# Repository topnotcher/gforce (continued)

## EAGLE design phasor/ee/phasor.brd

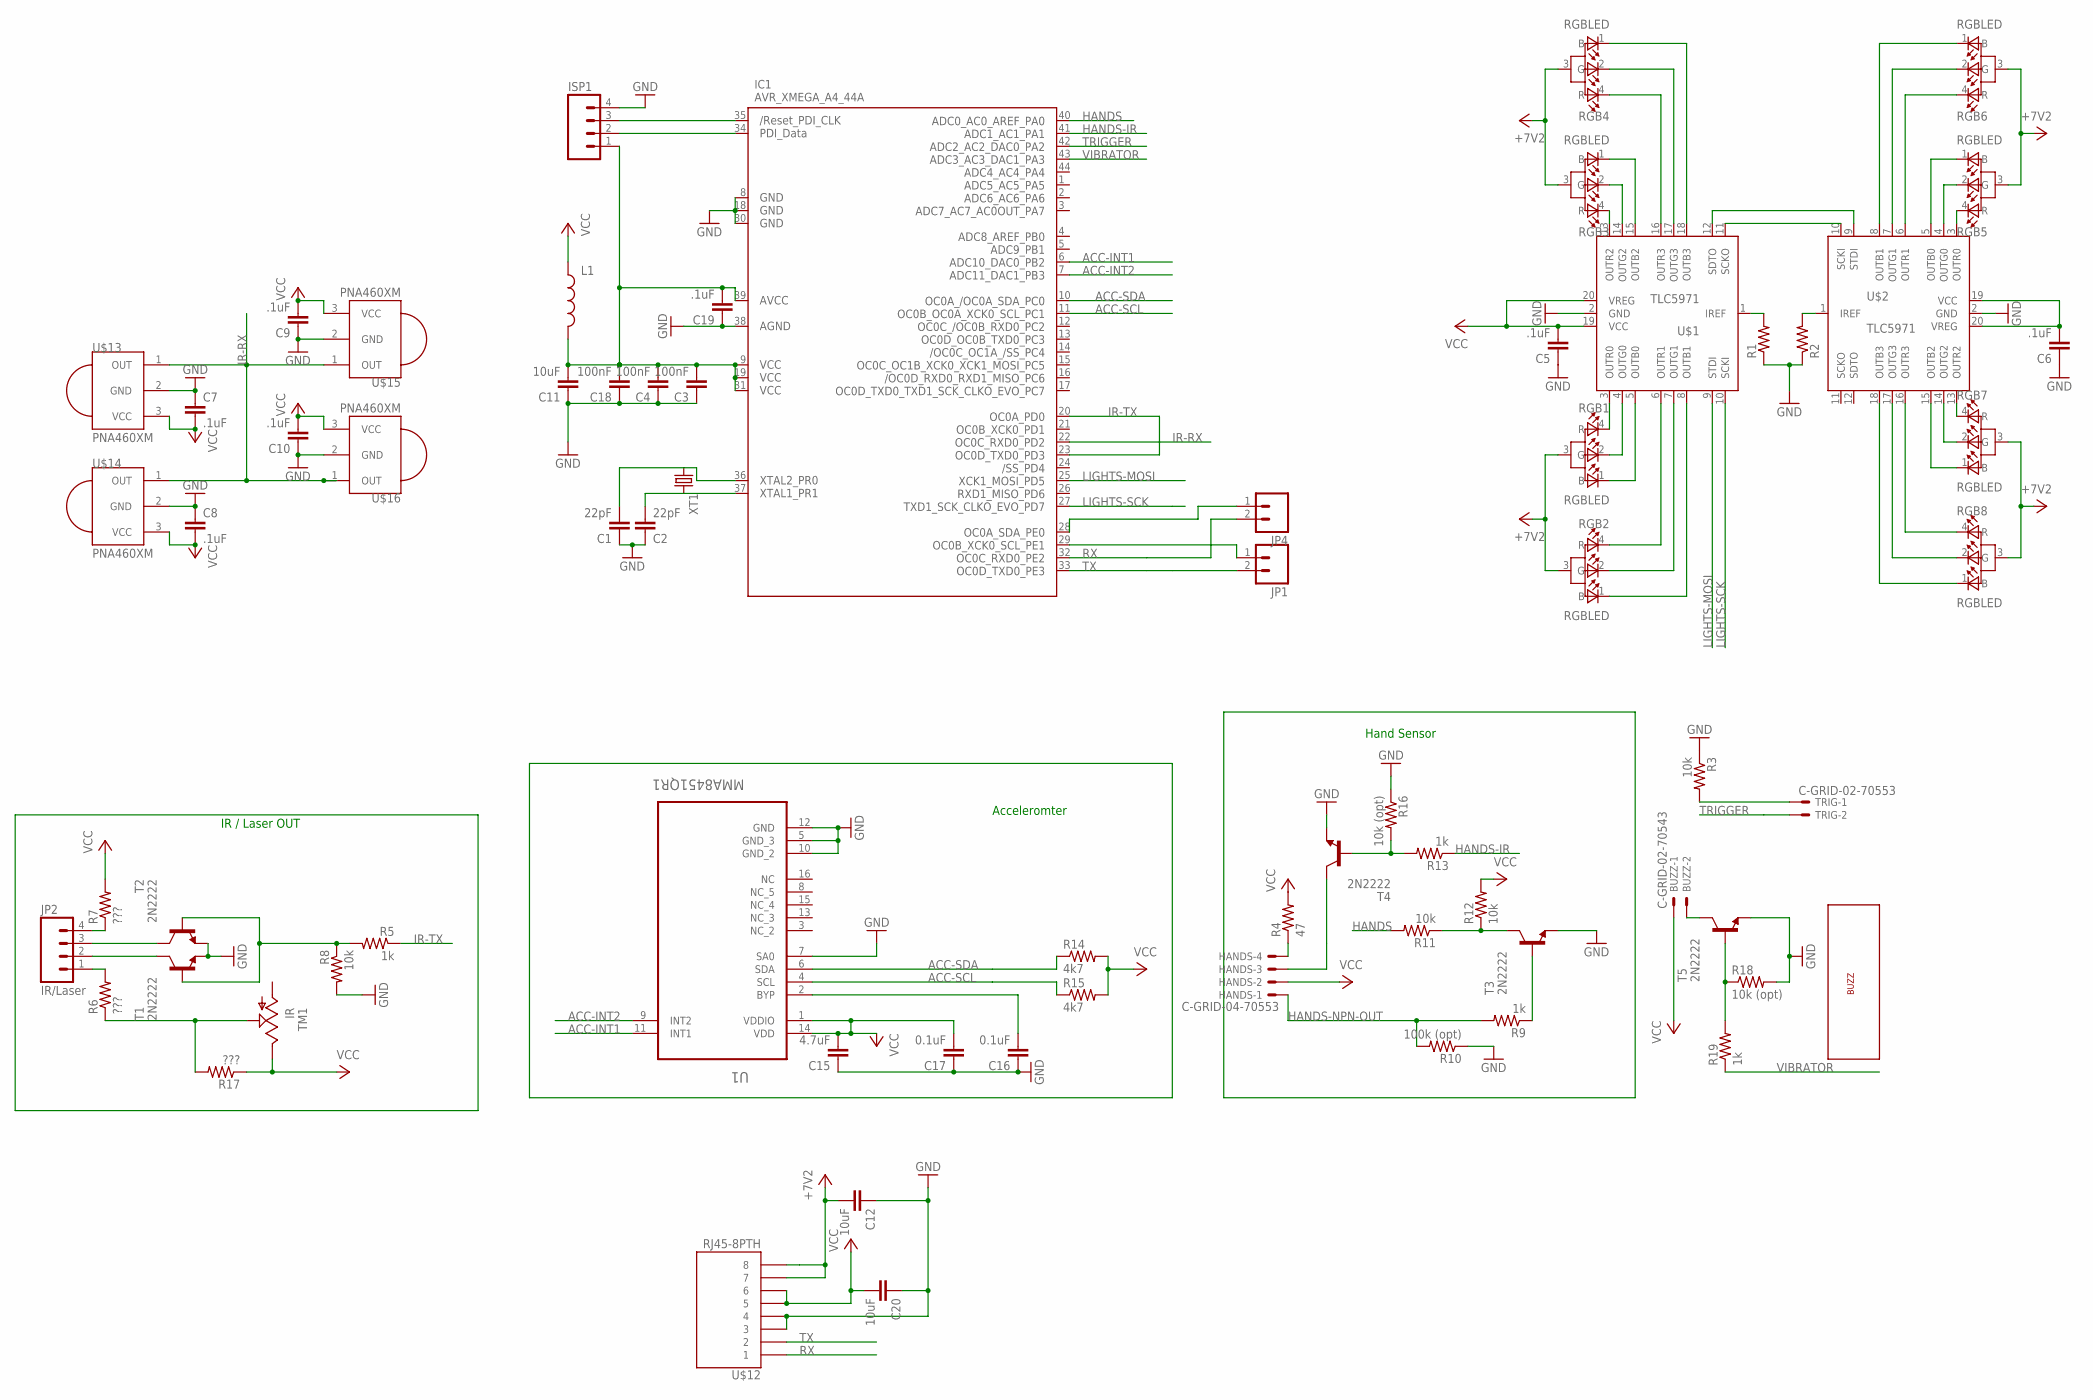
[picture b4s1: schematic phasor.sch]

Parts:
BUZZ: C-GRID-02-70543; 70543-02
C1, C2: 22pF; CAP-PTH-SMALL
C3, C4, C18: 100nF; 0603-CAP
C5, C6, C7, C8, C9, C10: .1uF; CAP-PTH-SMALL
C11, C12, C20: 10uF; 1206
C15: 4.7uF; 0805
C16, C17: 0.1uF; 0603-CAP
C19: .1uF; 0603-CAP
HANDS: C-GRID-04-70553; 70553-04
IC1: AVR_XMEGA_A4_44A; TQFP44
ISP1: M04LOCK; 1X04_LOCK
JP1, JP4: M02PTH; 1X02
JP2: IR/Laser; 1X04_LOCK
L1: INDUCTOR1206H*; 1206
R1, R2: R-US_0204/7; 0204/7
R3, R8, R11, R12: 10k; 0204/7
R4: 47; 0204/7
R5, R9, R13, R19: 1k; 0204/7
R6, R7, R17: ???; 0204/7
R10: 100k (opt); 0204/7
R14, R15: 4k7; 0204/7
R16, R18: 10k (opt); 0204/7
RGB1, RGB2, RGB3, RGB4, RGB5, RGB6, RGB7, RGB8: RGBLED; RGB-LED-10MM-COMMON-ANODE
T1, T2, T3, T4, T5: 2N2222; TO92-EBC-OVAL
TM1: IR; B25P
TRIG: C-GRID-02-70553; 70553-02
U1: MMA8451QR1; QFN50P300X300X100-16N
U$1, U$2: TLC5971; SSOP20
U$3: VIB-CAPSULE
U$12: RJ45-8PTH; RJ45-8
U$13, U$14, U$15, U$16: PNA460XM
XT1: CRYSTALHC49US; HC49US

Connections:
+7V2: C12.2, RGB1.3 (VCC), RGB2.3 (VCC), RGB3.3 (VCC), RGB4.3 (VCC), RGB5.3 (VCC), RGB6.3 (VCC), RGB7.3 (VCC), RGB8.3 (VCC), U$12.7, U$12.8
ACC-INT1: IC1.6 (PB2), U1.11 (INT1)
ACC-INT2: IC1.7 (PB3), U1.9 (INT2)
ACC-SCL: IC1.11 (PC1), R15.1, U1.4 (SCL)
ACC-SDA: IC1.10 (PC0), R14.1, U1.6 (SDA)
GND: C1.1, C2.1, C3.1, C4.1, C5.1, C6.1, C7.1, C8.1, C9.1, C10.1, C11.1, C12.1, C15.1, C16.1, C17.1, C18.1, C19.1, C20.1, IC1.8 (GND1), IC1.18 (GND2), IC1.30 (GND3), IC1.38 (AGND), ISP1.4, R1.1, R2.1, R3.1, R8.2, R10.1, R16.1, R18.2, T1.E, T2.E, T3.E, T4.E, T5.E, U1.5 (GND_3), U1.7 (SA0), U1.10 (GND_2), U1.12 (GND), U$1.2 (GND), U$2.2 (GND), U$12.3, U$12.4, U$13.2 (GND), U$14.2 (GND), U$15.2 (GND), U$16.2 (GND)
HANDS: IC1.40 (PA0), R11.2
HANDS-IR: IC1.41 (PA1), R13.1
HANDS-NPN-OUT: HANDS.1, R9.2, R10.2
IR-RX: IC1.22 (PD2), U$13.1 (OUT), U$14.1 (OUT), U$15.1 (OUT), U$16.1 (OUT)
IR-TX: IC1.20 (PD0), IC1.23 (PD3), R5.1
LIGHTS-MOSI: IC1.25 (PD5), U$1.9 (STDI)
LIGHTS-SCK: IC1.27 (PD7), U$1.10 (SCKI)
unnamed: U$1.11 (SCKO), U$2.10 (SCKI)
unnamed: U$1.12 (SDTO), U$2.9 (STDI)
unnamed: R1.2, U$1.1 (IREF)
unnamed: RGB1.4 (R), U$1.3 (OUTR0)
unnamed: RGB1.2 (G), U$1.4 (OUTG0)
unnamed: RGB1.1 (B), U$1.5 (OUTB0)
unnamed: RGB2.4 (R), U$1.6 (OUTR1)
unnamed: RGB2.2 (G), U$1.7 (OUTG1)
unnamed: RGB2.1 (B), U$1.8 (OUTB1)
unnamed: RGB3.1 (B), U$1.15 (OUTB2)
unnamed: RGB3.4 (R), U$1.13 (OUTR2)
unnamed: IC1.29 (PE1), JP1.1
unnamed: RGB4.4 (R), U$1.16 (OUTR3)
unnamed: BUZZ.2, T5.C
unnamed: RGB4.1 (B), U$1.18 (OUTB3)
unnamed: RGB5.4 (R), U$2.3 (OUTR0)
unnamed: RGB5.2 (G), U$2.4 (OUTG0)
unnamed: RGB5.1 (B), U$2.5 (OUTB0)
unnamed: R18.1, R19.2, T5.B
unnamed: RGB6.2 (G), U$2.7 (OUTG1)
unnamed: RGB6.1 (B), U$2.8 (OUTB1)
unnamed: RGB8.4 (R), U$2.16 (OUTR3)
unnamed: RGB8.2 (G), U$2.17 (OUTG3)
unnamed: RGB8.1 (B), U$2.18 (OUTB3)
unnamed: RGB7.1 (B), U$2.15 (OUTB2)
unnamed: RGB7.2 (G), U$2.14 (OUTG2)
unnamed: RGB7.4 (R), U$2.13 (OUTR2)
unnamed: C2.2, IC1.37 (PR1), XT1.2
unnamed: C1.2, IC1.36 (PR0), XT1.1
unnamed: R3.2, TRIG.1
unnamed: R6.1, R17.2, TM1.S
unnamed: HANDS.4, R4.1
unnamed: R9.1, T3.B
unnamed: R11.1, R12.1, T3.C
unnamed: R2.2, U$2.1 (IREF)
unnamed: C16.2, U1.2 (BYP)
unnamed: HANDS.3, T4.C
unnamed: JP2.1, R6.2
unnamed: JP2.2, T1.C
unnamed: JP2.4, R7.1
unnamed: JP2.3, T2.C
unnamed: R5.2, R8.1, T1.B, T2.B
unnamed: IC1.28 (PE0), JP4.1
unnamed: IC1.34 (PDI_DATA), ISP1.2
unnamed: R13.2, R16.2, T4.B
unnamed: IC1.35 (RESET), ISP1.3
unnamed: C3.2, C4.2, C11.2, C18.2, C19.2, IC1.9 (VCC1), IC1.19 (VCC2), IC1.31 (VCC3), IC1.39 (AVCC), ISP1.1, L1.2
RGB3: RGB3.2 (G), U$1.14 (OUTG2)
RGB4: RGB4.2 (G), U$1.17 (OUTG3)
RGB6: RGB6.4 (R), U$2.6 (OUTR1)
RX: IC1.32 (PE2), JP4.2, U$12.1
TRIGGER: IC1.42 (PA2), TRIG.2
TX: IC1.33 (PE3), JP1.2, U$12.2
VCC: BUZZ.1, C5.2, C6.2, C7.2, C8.2, C9.2, C10.2, C15.2, C17.2, C20.2, HANDS.2, L1.1, R4.2, R7.2, R12.2, R14.2, R15.2, R17.1, TM1.E, U1.1 (VDDIO), U1.14 (VDD), U$1.19 (VCC), U$1.20 (VREG), U$2.19 (VCC), U$2.20 (VREG), U$12.5, U$12.6, U$13.3 (VCC), U$14.3 (VCC), U$15.3 (VCC), U$16.3 (VCC)
VIBRATOR: IC1.43 (PA3), R19.1

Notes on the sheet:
IR / Laser OUT
Hand Sensor
Acceleromter

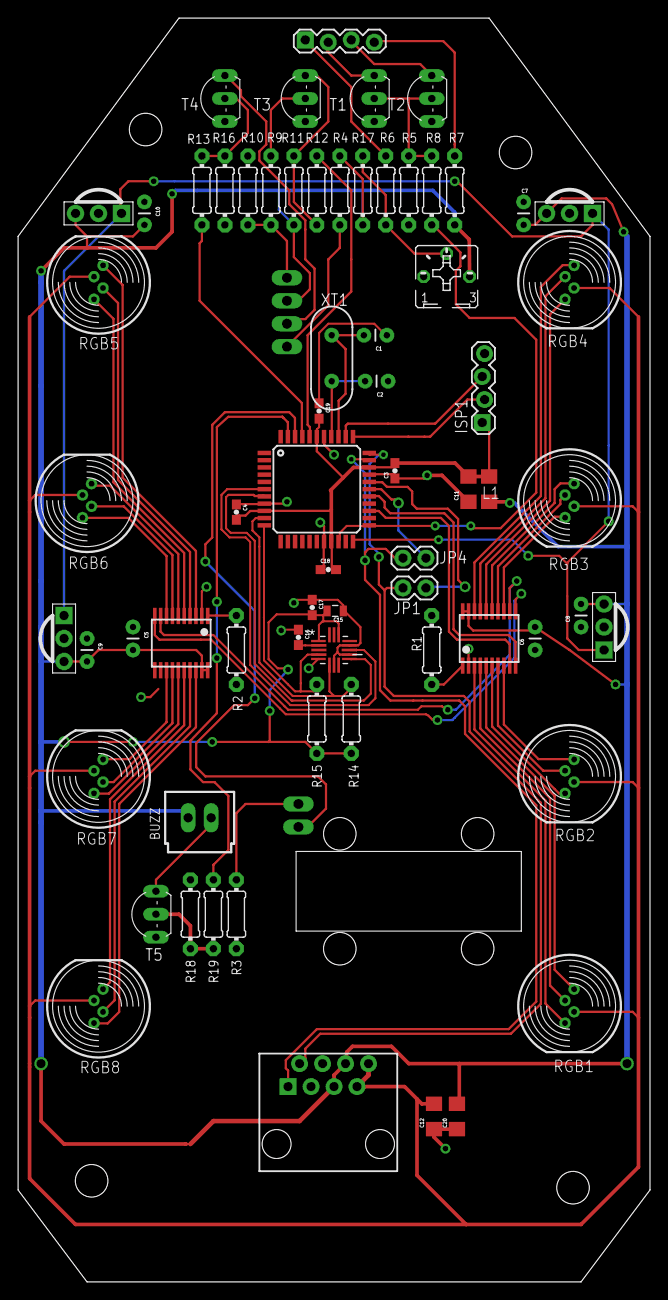
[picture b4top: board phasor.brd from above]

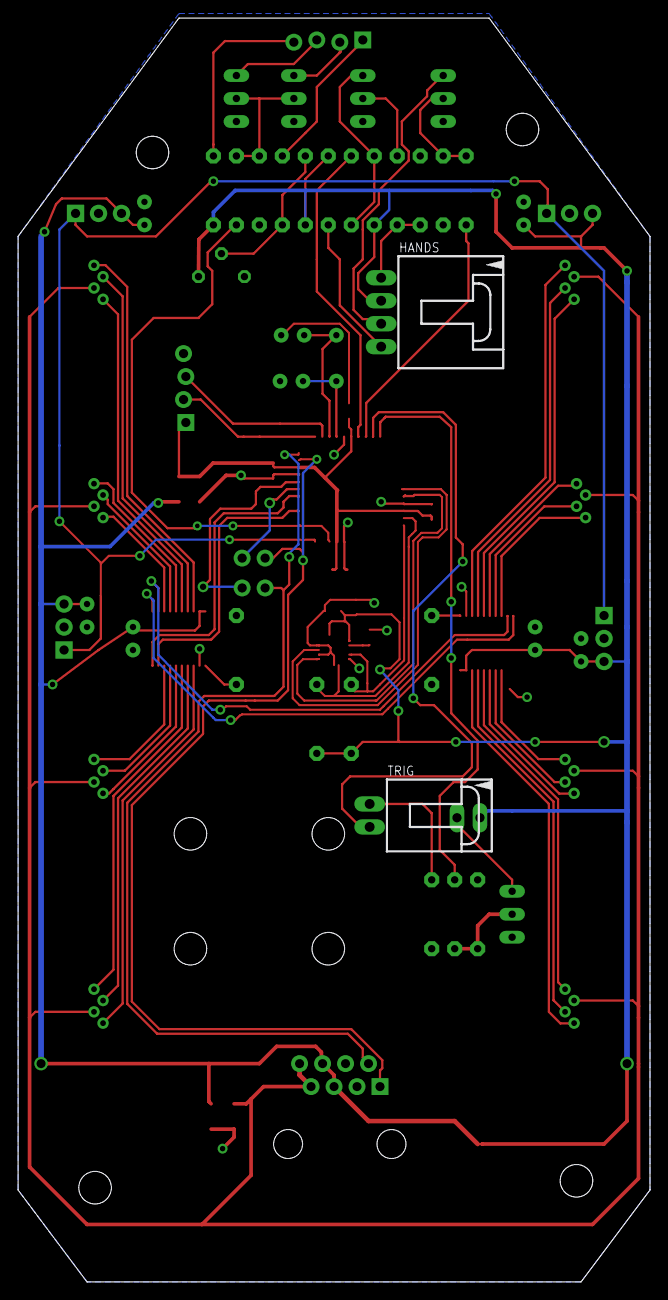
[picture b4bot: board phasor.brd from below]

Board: 2 copper layers, 69.8 x 139.7 mm, 70 parts (2 on the bottom side), 68 nets.

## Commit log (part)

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2014-02-20 derp broken fuck
2014-02-20 Update to support read/write with repeated start
2014-02-20 check ping CRC, ping phasor
2014-02-22 change programmer to jtag3pdi from avrispmkii
2014-02-22 Move eventq files to include/
2014-02-22 Fix mpc src address issues with the phasor
2014-02-23 change gs to a command line
    Receives from GF non-blocking and uses a readline command line
2014-02-23 put system clock initialization in a function
2014-02-23 dumb comments
2014-02-23 Update to work with new comm interface
2014-02-23 fix deac handling
    - set game state to inactive when deaced
    - set countdown_cb to player_activate
2014-03-01 Add trigger support
    trigger presses detected by phasor, sent to master. Master processes
    trigger press and sends IR to transmit back to phasor.
2014-03-02 fiddle with xbee flow control and sleep mode
2014-03-07 Read iButton serial number
    Uses a state machine to send a sequence of commands to the DS2483 in
    order to read the 8 bytes of the serial number from an iButton.
2014-03-07 Make TWI master retry the transaction on NAKs
2014-03-07 Missing one wire wait
2014-03-07 remove unused functions
2014-03-07 Fix unreliable ibutton reading
    Issue introduced in 5811cb857c3ae68193d6205f5268e5208a29e357
    I can't explain this, but there appears to be a timing issue...
2014-03-08 move *_stack definitions to threads.c
2014-06-07 scheduler: fix timing inconsistencies.
    If the tick time is not a perfect multiple of the number of ticks
    remaining for the head task, the unsigned integer ticks might underflow,
    causing the task to stay queued indefinitely. Fix by checking if
    remaining_ticks <= ticks.
2014-06-07 scheduler: remove ATOMIC_BLOCK from scheduler_remove_node
    scheduler_remove_node is either called from SCHEDULER_RUN or
    scheduler_register. In the former case, interrupts are already disabled,
    so there's no need fir the atomic block. Instead only wrap
    scheduler_unregister
2014-10-11 scheduler: use doubly instead of singly linked list.
    Adds a bit of overhead to registering, but remove iterating through the
    list on removal.
2014-10-11 schedulre: use chunkpool
2014-10-11 chunkpool: uint8_t * chunkpool_acquire -> void * chunkpool_alloc
2014-10-11 mempool: comments
2014-10-11 timer: remove initialization of static
2014-10-11 mempool: macro to get mempool_block_t given the buffer
2014-10-11 timer: split up add_timer
2014-10-11 game: defer updating the display
    Running the display update directly via the scheduler causes it to be
    run in interrupt context; this defers it until after the interrupt.
2014-10-14 timer: handle list reordering more cleanly.
    Instead of reordering the list after tasks are run, simply recreate the
    list by adding tasks back. (There may be a larger performance overhead
    this way?)
2014-10-14 timer: remove uneeded "inline"s
2014-10-26 TWI: zero device memory before use.
2015-01-01 game: remove hard coded HZ values
2015-01-27 threads: generic block()
2016-04-05 uncrustify
2016-07-11 add header dependencies
2016-08-02 remove commented code
2016-08-03 threads: add a (make shift) idle task
    - temp: make tasks suspend and wake the main thread.
    - temp: make idle thread yield periodically
    - add thread_wake_and_schedule to schedule a thread and switch to the
    highest priority task.
2016-08-03 phasor: add board and schematic files
2016-08-12 move to FreeRTOS
    This is a really huge commit that really should have been split up :).
    - strip out old nasty threads.
    - make "tasks" use FreeRTOS queues.
    - make display transmit a task
    - Make LEDs a task
    - Stack overflows suck
2016-08-13 CMake all the things.
2016-08-16 remove old uart code
2016-08-16 part III: remove mpc_tx_process task
2016-08-16 part V: remove xbee tx task
2016-08-17 part VIII: rip out main_thread and task_schedule.
2016-08-18 part XI: remove main_thread and tasks from back
    - Make a thread for the charger...
    - This is horrible and needs fixing.
    - Derp derp
2016-08-19 game: delay booted message for 1 second
2016-08-19 diag: make simulated IR come from any board we want
2016-08-20 add back more code I accidentally removed :|
2016-08-25 remove unused include
2016-08-26 leds: make COLOR_ACTIVE configurable
    COLOR_ACTIVE can be changed to one of the other colors
2016-08-27 led: remove sclk_trigger() and reduce SPI frequency
    sclk_trigger() - not needed. We don't actually need to pulse the clock
    line -- just leave it level.
    Also the high frequency was triggering false data latches since it
    couldn't clock the bytes in fast enough.
2016-08-30 leds: use DMA when using USART in SPI master mode
2016-08-30 shoulder board: fix rev2 bugs
    - Bump board revision to rev3
    - Remove USART/SPI jumper - USART works fine
    - resolves GF-38
    - Fix ISP pin hole sizing
    - resolves GF-37
2016-08-31 lights: make boot pattern rotate through all colors
2016-09-01 leds: move some function declarations out of header
2016-09-02 leds: [part I] break TLC59711 driver out of LED pattern code
    - Instantiate a tlc59711_dev and pass in SPI driver.
    - functions to change tlc59711 settings/led colors
    - WAAAAY more sane.
    - Setting brightness is actually implemented correctly in the tlc59711
    driver; brightness control was wack (crazy wrong) before.
    - brightness control via the MPC command needs to be re-implemented
2016-11-30 mpc: Use constants for MPC_* commands
    - Use MPC_CMD_* instead of e.g. 'I'.
    - Define all the constants in a python file
    - add a custom cmake command to generate header file from python.
    - Eventually use python to communicate with vest.
2016-12-10 Update to use tamp streaming.
2016-12-11 Move structure definitions to python module
2016-12-12 Remove encapsulation for shot packets - forward directly.
2016-12-13 Strip encapsulation on ping replies
    - Also allow replies from master
2016-12-13 Almost writing acceptance tests.
2016-12-13 Loop inside collect().
2016-12-17 oops. Did I even build this?
2016-12-21 Implement stun disable.
2016-12-23 Bypass comm_send - use serialcomm directly. [comm rewrite: part 2]
2016-12-24 Separate serial-rx tasks serialcomm [comm rewrite: part 5]
2016-12-26 Rewrite SPI driver [comm rewrite: part 7]
2016-12-31 Fix misplaced #endif
2016-12-31 Remove old queue implementation.
2017-01-02 Use freertos timers.
2017-01-03 Decouple MPC from MPC/HW drivers.
2017-01-05 Used CRC function only used for IR into irrx.
2017-01-06 Remove old "game server" code. Ew.
2017-01-06 Move xmega-specific util.[ch] to bsp/xmega.
2017-01-07 Decouple LED transport (usart/spi) drivers from LED code.
2017-01-07 Move tlc59711 driver to drivers/
2017-01-07 Move unported code to PLATFORM_SOURCES.
2017-01-07 fixup! Ensure allocated memory is pointer aligned.
2017-01-07 fixup! Ensure allocated memory is pointer aligned.
    - Rather, maximally alligned.
2017-01-08 Add missing stub.
2017-01-08 Make the SAML21 build... build.
    - Vaaaaaaarious changes.
2017-01-08 Move build related files to build/
2017-01-08 Modify LED blinker to exercise scheduler.
2017-01-08 Move xmega system timer configuration to port.c
2017-01-17 Partially working I2C master.
2017-01-20 Inline twi_slave_direction
2017-01-20 Add a common TWI Master driver interface.
    - Break out common parts of SAML21 and XMEGA implementations into
    drivers/twi/master.
2017-01-21 Break ins and txn_complete out of twi_master_init
    - Add separate function to set these values
    - _init is device-specific, but the txn_complete callback needs to be
    generic.
2017-01-21 xmega: Move TWI Slave ISR handling into TWI Slave driver.
    - Rather than havning the interrupt vector defined ... elsewhere, create
    static table of TWIS device instances to they ISR can be called
    directly from the driver.
2017-01-21 saml21: Instantiate MPCTWI instance.
2017-01-21 Break clock configuration out of TWI drivers.
    - Still needs work to make the configuration more generic, and probably
    to allow passing it into the driver initializers.
2017-01-25 saml21: initial implementation of DMA for LED controller
2017-01-26 xmega: update led_spi driver to account for removal of tx_isr.
2017-01-26 xmega: Make master and slave drivers take TWI_t
    Rather than the TWI_SLAVE_t or TWI_MASTER_t - this allows consolidating
    the code to get the index number of the TWI module for use in the ISRs.
2017-01-26 xmega: Add __attribute__((signal)) to TWI mater/slave ISRs
2017-01-27 xmega: Get build working for master board.
    Also, this code appears to actually work, at least basically. WTF???
2017-01-28 xmega: Move usart driver interrupt handling into driver.
2017-01-29 xmega: Add a basic DMA driver.
    - Allocate DMA channels, automatically enabling the controller.
    - Set source and dest addrs.
2017-01-29 xmega: Move led_usart_dma_get_trigsrc to uart driver.
2017-01-29 xmega: Add interrupt handling to DMA driver.
2017-08-12 twi: Fix a syntax error.
    DID I EVEN RUN THIS CODE???!?!?!?!
    ... Did I even compile this code? What code is running on the MCU
    now?!?!?!
2017-10-06 Remove -fpack-struct and -fshort-enum for SAML21
2017-11-22 charger: add ee files.
2017-11-23 build: Increase stack size on SAML21E17B.
    - start at the end of ram.
    - Seems to fix a stack overflow that was apparently occuring after
    removing -fpack-struct. Unsure how so much stack space is being used
    :|.
2017-11-24 phaser: remove no longer necessary configuration
2017-12-26 [build] make programmer variables options
2018-01-20 game: Disable trigger while inactive/stunned.
2018-04-09 sam: Change most "SAML21" references to "SAM"
    - drivers/saml21 all moved to drivers/sam.
    - ARM toolchain file split into toolchain file and SAM target file.
    - SAML21 definitions moved to saml21.cmake.
    - Will it build on SAMD51? I wonder...
2018-04-09 cmake: Build Debug with -O0
    STOP OPTIMIZING MY FUCKING VARIABLES AWAY.
2018-04-09 saml21: Add one include to include all SAM headers.
    Rather than including saml21/io.h, add sam.h which will include the
    appropriate headers for the given part. This is in preparation for
    supporting the SAMD51.
2018-04-09 samd51: check in cortex M4 headers
2018-04-09 samd51: Define required symbols in linker script.
    __stack_top, __heap_start used by existing code.
2020-03-13 sam: Change part from samd51p20a to samd51n20a
    I don't know why I had samd51p20a when I think the schematic always had
    samd51n20a.
2020-03-13 samd51: Hook up the FreeRTOS ISRs.
2020-03-13 dma: Update DMA driver for SAMD51
2020-03-13 sam: add function to set pin muxes
2020-03-13 config: Define all the PinMux settings in one place.
2020-03-13 samd51: Update SAMD51 pack from atmel
2020-03-13 debug: Add some stuff for semihosting.
    This can stay here fo now until I decide to do something with it...
2020-03-13 sercom: add function to get sercom index from pointer.
2020-03-13 mpc: Change registered drivers to a linked list.
2020-03-13 mpc: Make back/master the same address.
    - Add a loopback driver so it can talk to itself. In theory all the code
    just works TM
2020-03-14 sercom: Unify interrupt handling; works on SAML21 and SAMD51
    (not that I have tested on SAML21, or with interrupt line 3...)
    SAML21 has one interrupt line per sercom; SAMD51 has four. The first
    four interrupt flags use dedicated lines while the remainder are
    multiplexed in the 4th. SAML21 multiplexes all of them in one handler.
    This moves all of the handling of those to the sercom driver.
2020-03-14 fixup! sercom: Unify interrupt handling; works on SAML21 and SAMD51
2020-03-24 isr: fix vector table alignment.
2020-03-26 sdhc: make initialization function extern.
2020-03-26 sound: Play mp3s from SD card via I2S.
2020-03-26 freertos: tweak config
    - Better interrupt priorities
    - preemption
    - mutexes
    - function to get current task handle
2020-03-26 sound: add fatfs, mp3, sdhc files to build.
2020-03-26 python: Convert server to TCP.
2020-03-26 mpcipc: Copy transmitted packets to avoid losing them.
    We lose custody of the buffer when the send function returns, thus a
    copy must be made.
2020-03-26 game: Include master in the all boards list.
    This _is_ master, but it needs to talk to itself via IPC.
    Also remove the lights_booting() hack that was masking a real issue.
